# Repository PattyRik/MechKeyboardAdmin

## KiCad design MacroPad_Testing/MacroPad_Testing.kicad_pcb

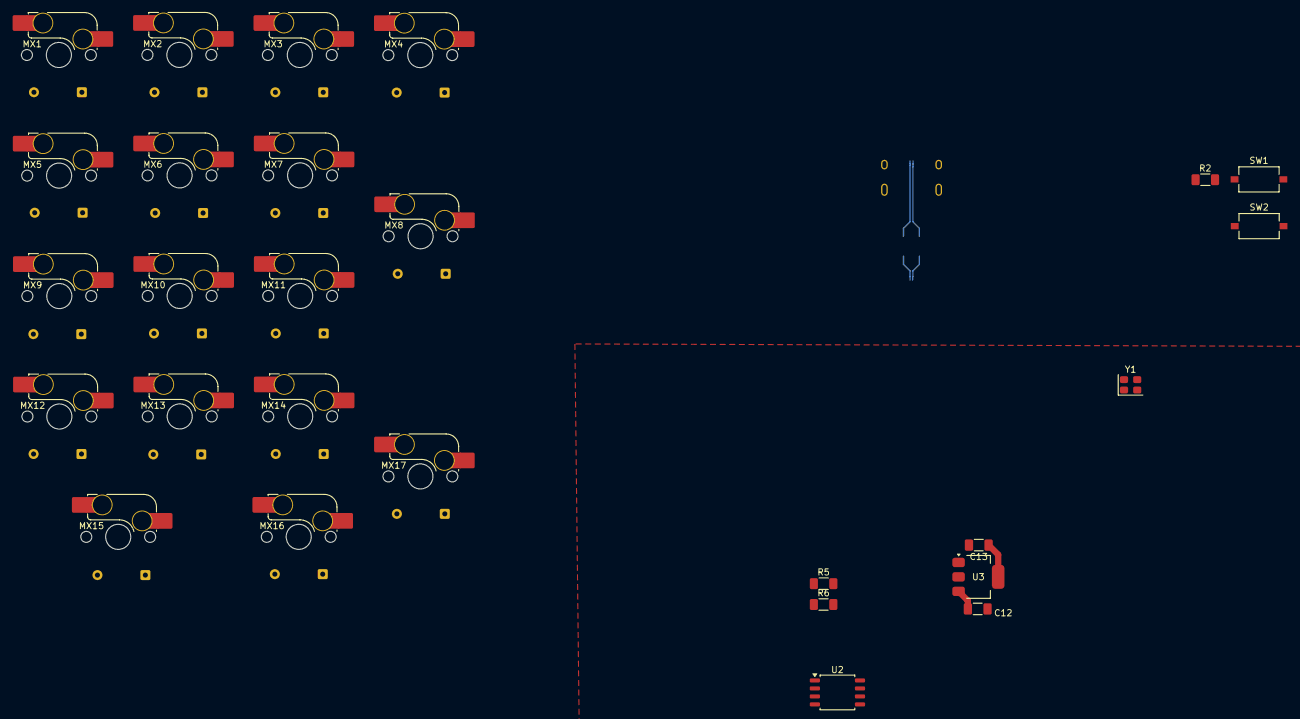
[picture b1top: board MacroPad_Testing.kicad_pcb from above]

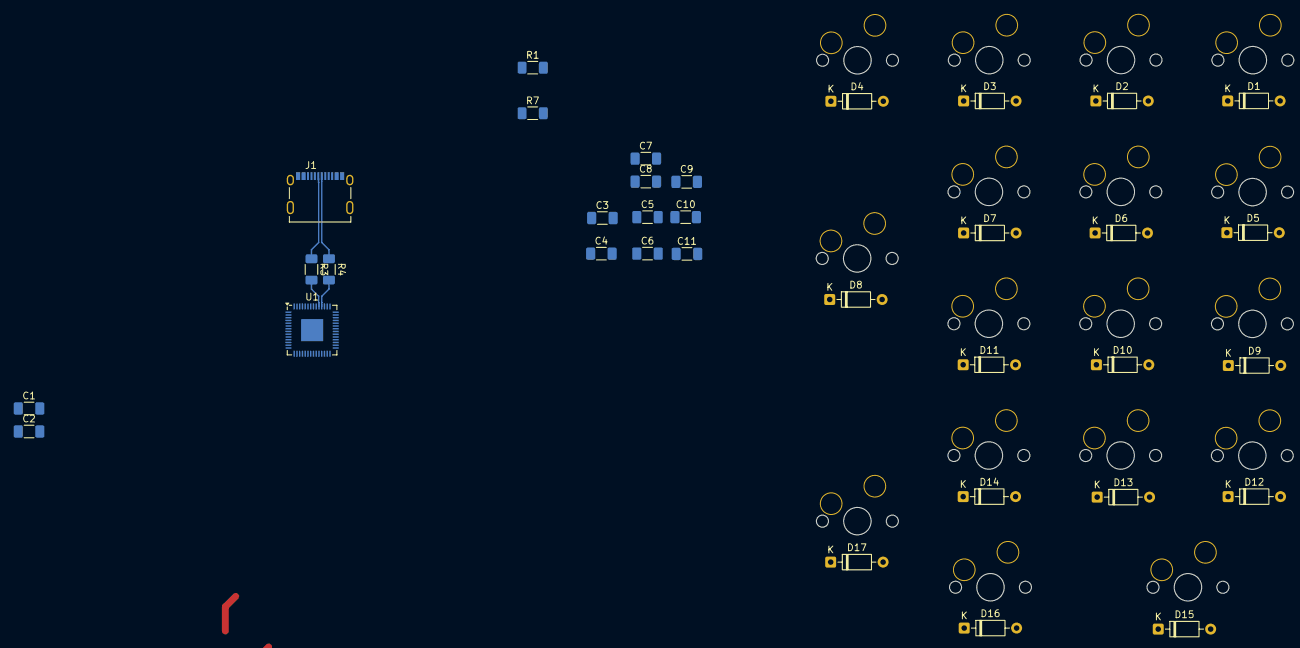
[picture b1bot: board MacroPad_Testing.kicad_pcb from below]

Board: 2 copper layers, 61 parts (34 on the bottom side), 48 nets.

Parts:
C1, C2: 18p; C_1206_3216Metric_Pad1.33x1.80mm_HandSolder
C3, C4: 1u; C_1206_3216Metric_Pad1.33x1.80mm_HandSolder
C5, C6, C7, C8, C9, C10, C11: 100n; C_1206_3216Metric_Pad1.33x1.80mm_HandSolder
C12, C13: 10u; C_1206_3216Metric_Pad1.33x1.80mm_HandSolder
D1, D2, D3, D4, D5, D6, D7, D8, D9, D10, D11, D12, D13, D14, D15, D16, D17: 1N4148; D_DO-35_SOD27_P7.62mm_Horizontal
J1: USB_C_Receptacle_USB2.0_14P; AMPHENOL_10171746-00021LF
MX1: Num Lock; SW_MX_HS_CPG151101S11_1u
MX2: Forward Dash; SW_MX_HS_CPG151101S11_1u
MX3: Asterisk; SW_MX_HS_CPG151101S11_1u
MX4: Minus; SW_MX_HS_CPG151101S11_1u
MX5: Seven; SW_MX_HS_CPG151101S11_1u
MX6: Eight; SW_MX_HS_CPG151101S11_1u
MX7: Nine; SW_MX_HS_CPG151101S11_1u
MX8: Plus (2u Vert); SW_MX_HS_CPG151101S11_1u
MX9: Four; SW_MX_HS_CPG151101S11_1u
MX10: Five; SW_MX_HS_CPG151101S11_1u
MX11: Six; SW_MX_HS_CPG151101S11_1u
MX12: One; SW_MX_HS_CPG151101S11_1u
MX13: Two; SW_MX_HS_CPG151101S11_1u
MX14: Three; SW_MX_HS_CPG151101S11_1u
MX15: Zero (2u Hor); SW_MX_HS_CPG151101S11_1u
MX16: Del; SW_MX_HS_CPG151101S11_1u
MX17: Enter (2u Vert); SW_MX_HS_CPG151101S11_1u
R1, R5, R6, R7: 5k1; R_1206_3216Metric_Pad1.30x1.75mm_HandSolder
R2: 1k PD; R_1206_3216Metric_Pad1.30x1.75mm_HandSolder
R3, R4: 27; R_1206_3216Metric_Pad1.30x1.75mm_HandSolder
SW1: BOOTSEL; SW_Tactile_SPST_NO_Straight_CK_PTS636Sx25SMTRLFS
SW2: Reset; SW_Tactile_SPST_NO_Straight_CK_PTS636Sx25SMTRLFS
U1: RP2040; QFN-56-1EP_7x7mm_P0.4mm_EP3.2x3.2mm
U2: W25Q128JVS; SOIC-8_5.3x5.3mm_P1.27mm
U3: NCP1117-1.5_SOT223; SOT-223-3_TabPin2
Y1: ABM8-12MHz; Oscillator_SMD_Abracon_ASE-4Pin_3.2x2.5mm

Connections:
/3V3: C4.1, C5.1, C6.1, C7.1, C8.1, C9.1, C10.1, C11.1, C13.1, R7.1, U1.1 (IOVDD), U1.10 (IOVDD), U1.22 (IOVDD), U1.33 (IOVDD), U1.42 (IOVDD), U1.43 (ADC_AVDD), U1.44 (VREG_VIN), U1.48 (USB_VDD), U1.49 (IOVDD), U2.8 (VCC), U3.2 (VO)
/Matrix col 0: MX1.1, MX5.1, MX9.1, MX12.1, MX15.1, U1.8 (GPIO6)
/Matrix col 1: MX2.1, MX6.1, MX10.1, MX13.1, MX16.1, U1.9 (GPIO7)
/Matrix col 2: MX3.1, MX7.1, MX11.1, MX14.1, MX17.1, U1.11 (GPIO8)
/Matrix col 3: MX4.1, MX8.1, U1.12 (GPIO9)
/Matrix row 0: D1.1 (K), D2.1 (K), D3.1 (K), D4.1 (K), U1.2 (GPIO0)
/Matrix row 1: D5.1 (K), D6.1 (K), D7.1 (K), D8.1 (K), U1.3 (GPIO1)
/Matrix row 2: D9.1 (K), D10.1 (K), D11.1 (K), U1.4 (GPIO2)
/Matrix row 3: D12.1 (K), D13.1 (K), D14.1 (K), U1.5 (GPIO3)
/Matrix row 4: D15.1 (K), D16.1 (K), D17.1 (K), U1.6 (GPIO4)
/RP2040/1V1: C3.1, U1.23 (DVDD), U1.45 (VREG_VOUT), U1.50 (DVDD)
/RP2040/QSPI_CS: R1.2, R2.2, U1.56 (~QSPI_SS), U2.1 (~CS)
/RP2040/QSPI_SCLK: U1.52 (QSPI_SCLK), U2.6 (CLK)
/RP2040/QSPI_SD0: U1.53 (QSPI_SD0), U2.5 (DI/IO_{0})
/RP2040/QSPI_SD1: U1.55 (QSPI_SD1), U2.2 (DO/IO_{1})
/RP2040/QSPI_SD2: U1.54 (QSPI_SD2), U2.3 (~WP/IO_{2})
/RP2040/QSPI_SD3: U1.51 (QSPI_SD3), U2.7 (~HOLD/~RESET/IO_{3})
/RP2040/USB D+: R3.2, U1.47 (USB_DP)
/RP2040/USB D-: R4.2, U1.46 (USB_DM)
/USB_D+: J1.A6 (D+), J1.B6 (D+), R3.1
/USB_D-: J1.A7 (D-), J1.B7 (D-), R4.1
GND: C1.1, C2.2, C3.2, C4.2, C12.2, C13.2, R5.1, R6.1, SW1.2, SW2.2, U1.19 (TESTEN), U1.57 (GND), U2.4 (GND), U3.1 (GND), Y1.2 (GND), Y1.4 (GND)
unnamed: C5.2, C6.2, C7.2, C8.2, C9.2, C10.2, C11.2
unnamed: D1.2 (A), MX1.2
unnamed: D2.2 (A), MX2.2
unnamed: D3.2 (A), MX3.2
unnamed: D4.2 (A), MX4.2
unnamed: D5.2 (A), MX5.2
unnamed: D6.2 (A), MX6.2
unnamed: D7.2 (A), MX7.2
unnamed: D8.2 (A), MX8.2
unnamed: D9.2 (A), MX9.2
unnamed: D10.2 (A), MX10.2
unnamed: D11.2 (A), MX11.2
unnamed: D12.2 (A), MX12.2
unnamed: D13.2 (A), MX13.2
unnamed: D14.2 (A), MX14.2
unnamed: D15.2 (A), MX15.2
unnamed: D16.2 (A), MX16.2
unnamed: D17.2 (A), MX17.2
unnamed: J1.A5 (CC1), R6.2
unnamed: J1.B5 (CC2), R5.2
unnamed: R1.1, R7.2
unnamed: R2.1, SW1.1
unnamed: SW2.1, U1.26 (RUN)
unnamed: C2.1, U1.20 (XIN), Y1.1 (IN)
unnamed: C1.2, U1.21 (XOUT), Y1.3 (OUT)
unnamed: C12.1, U3.3 (VI)
